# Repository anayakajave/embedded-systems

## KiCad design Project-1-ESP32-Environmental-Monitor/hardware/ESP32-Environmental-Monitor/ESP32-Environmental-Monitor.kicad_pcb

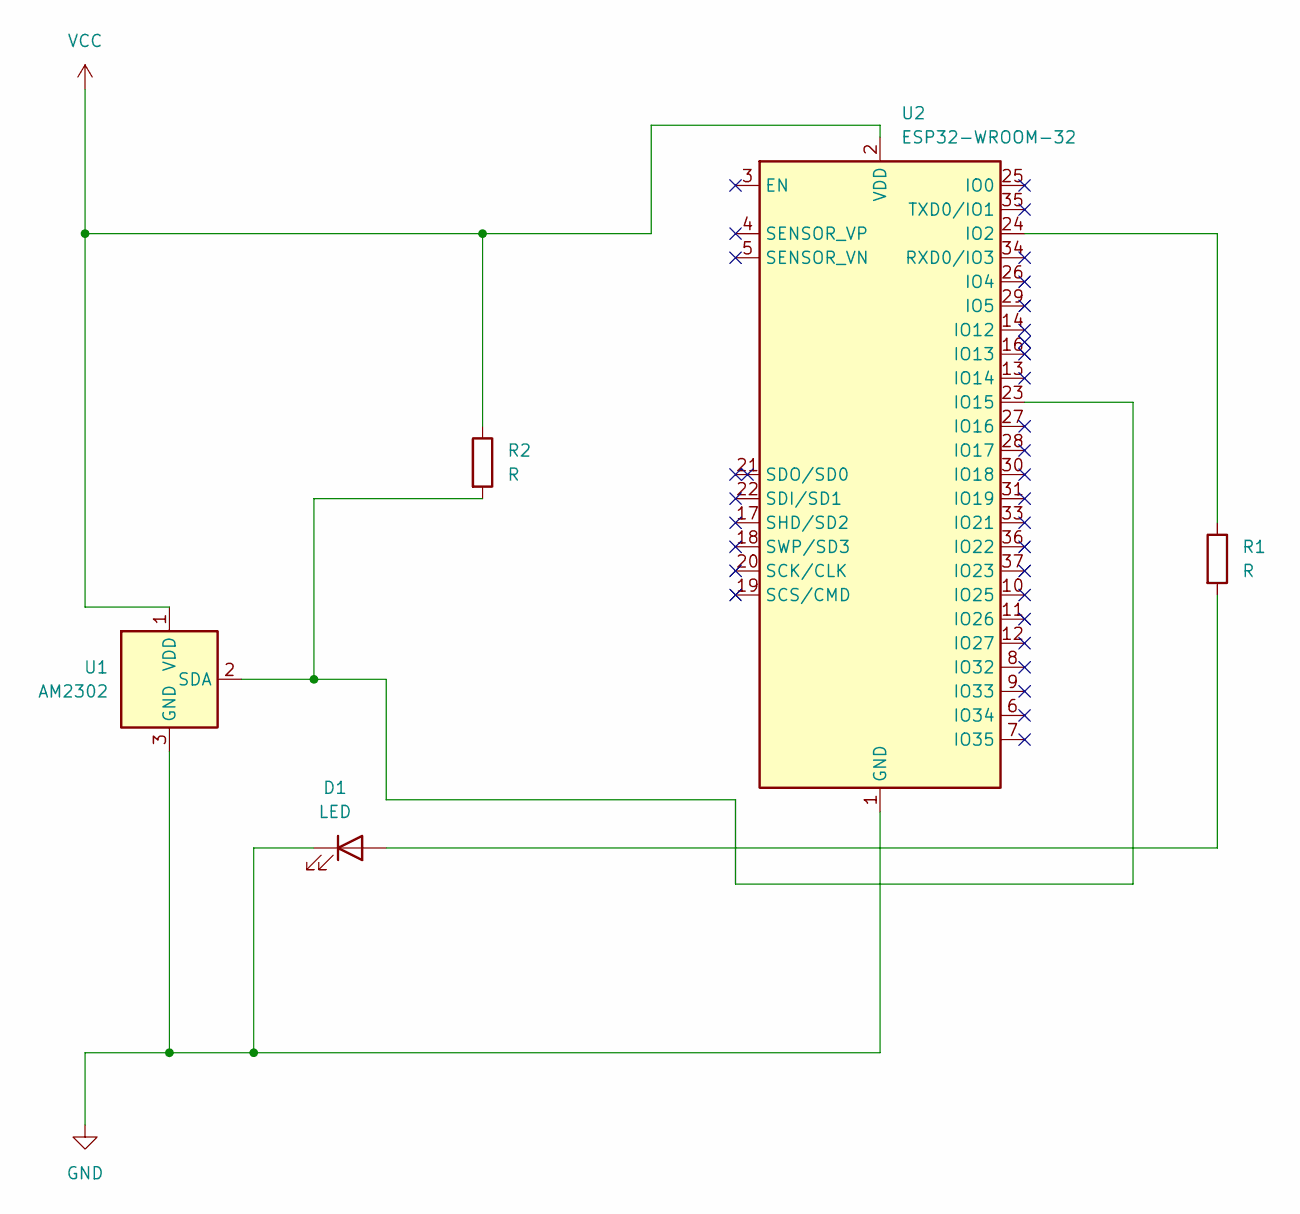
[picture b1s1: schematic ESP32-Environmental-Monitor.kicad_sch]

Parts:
D1: LED; LED_0805_2012Metric
R1, R2: R; R_0805_2012Metric
U1: AM2302; ASAIR_AM2302_P2.54mm_Vertical
U2: ESP32-WROOM-32

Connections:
GND: D1.1 (K), U1.3 (GND), U1.4 (GND), U2.1 (GND), U2.15 (GND), U2.38 (GND), U2.39 (GND)
unnamed: D1.2 (A), R1.2
unnamed: R2.2, U1.2 (SDA), U2.23 (IO15)
unnamed: R1.1, U2.24 (IO2)
VCC: R2.1, U1.1 (VDD), U2.2 (VDD)

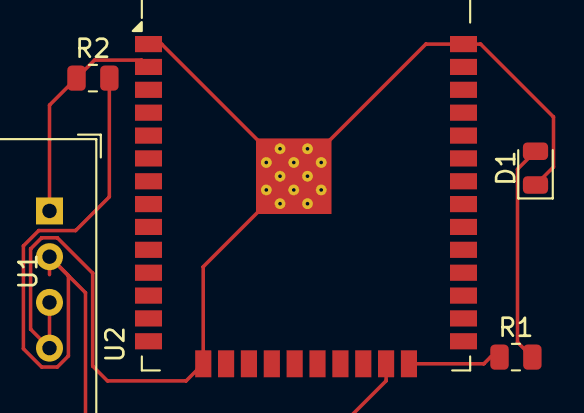
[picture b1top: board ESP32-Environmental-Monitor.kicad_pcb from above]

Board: 2 copper layers, 5 parts (0 on the bottom side), 5 nets.

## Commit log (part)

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2026-06-27 Initial commit: Add project structure and README
2026-06-27 Update README with project details
2026-06-30 Add ESP32 LED blink firmware
